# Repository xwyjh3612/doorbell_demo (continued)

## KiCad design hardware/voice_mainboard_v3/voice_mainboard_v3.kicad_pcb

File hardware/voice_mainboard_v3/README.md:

# 语音对讲V3主板工程

本版已完成可编辑的KiCad 9原理图、100×75mm四层PCB及实际装配BOM。独立检查通过：**ERC 0、DRC 0、未连接0，490项引脚/网络映射与原理图、PCB一致**。这是首板工程复核版本，尚未完成电源、封装、装配与整机验收，尚未生产放行。

板上直接焊ML307R-DL，集成充电、备用升压、自动电源切换、欠压控制和电池采样。ESP32-S3、INMP441、MAX98357沿用完整模块，通过线束连接。本版费用已经将这些外挂模块单独计入“主板总成”；当前架构还没有达到80元整机目标。

## 查看设计

- [交互预览](exports/review.html)：实际PCB正反面、接口、供电路径、检查范围与费用。
- [工程入口](voice_mainboard_v3.kicad_pro)、[PCB](voice_mainboard_v3.kicad_pcb)、[原理图](voice_mainboard_v3.kicad_sch)。
- [原理图SVG](exports/schematic/voice_mainboard_v3.svg)：网络标签同名即连接。
- [独立检查结果](exports/validation.json)、[DRC报告](exports/current-drc.json)、[ERC报告](exports/erc.json)。
- [实际局部走线及条件功率核算](exports/power-audit.json)：去耦电容角色、走线长度和明确的估算边界。
- [费用表](../../outputs/voice-v3-20261122/语音对讲V3主板费用.xlsx)、[费用说明](cost/费用说明.md)。
- [网站价格复核与降本候选](cost/网站价格复核与降本候选.md)：重新查询36个料号，区分原型号公开价、便宜候选及未取得的采购阶梯价。
- [ML307阶梯价修正及型号对比](cost/ML307阶梯价修正及型号对比.md)：用户提供完整档位后，确认R-DL的16.50元是1000只价格；5只和100只费用已修正，C-DL尚未批准替换。
- [50元量产主板目标](cost/50元量产主板目标.md)：按1000台、含ESP32/4G/音频及UPS制定控制目标；尚未完成对应集成设计、报价及实机验证，不能作为已实现成本。
- [工程复核包](exports/voice-v3-engineering-review.zip)：KiCad、Gerber/钻孔、BOM、坐标与检查证据；制造文件尚未生产放行。
- [装配BOM](cost/assembly-bom.csv)、[SMT坐标](cost/positions.csv)、[物料和工艺数据](cost/bom-and-process.json)。
- [工程复核及首板验收](工程复核及首板验收.md)：未完成项目与分步上电办法。

176个封装包括4个机械孔、11个测试点；默认装配128个SMT器件、23个插件，另10个器件DNP。49种SMT物料共431个电气焊点；8种插件共97个物理焊点，开关四条腿均计入插件人工。电池端子为插件，裸模组及自建电源芯片封装的SMT属性已补全；原生坐标导出的128项与实际BOM逐项核对。

## 供电与UPS

```text
4.5～5.5V圆口 -> F1 -> Q6 -> VIN_PROTECTED -> TPS2117 VIN1
受保护1S电池 -> TPS61230A约4.992V -> TPS2117 VIN2
TPS2117 -> JP4 2-3 -> POWER_BUS
POWER_BUS -> TPS62933P约3.792V -> J19 1-2 -> ML307 VBAT
POWER_BUS -> TPS63061固定5V -> JP1 1-2 -> SYS_5V
SYS_5V -> JP3 1-2 -> ESP32；另供功放和可选雷达
VIN_PROTECTED -> TP4056 100mA -> 受保护1S电池
```

输入为5.5mm外径/2.5mm中心的圆口，中心正极，标称5V/2A。F1为4A PTC，选该额定值用于温度降额余量，整机适配器基准仍是2A。Q6采用在低栅压有明确导通电阻规格的DMP2035U；ML307裸模组始终使用约3.8V支路。

就近备用升压输入去耦为C41，C40另作输入储能。已测保存PCB的局部走线路径并计算条件功率预算。5V/2A不足以承诺模组2A、系统350mA及100mA充电的同时持续满载；4.5V输入下的模组稳压余量也未通过实测。标称电源和瞬时模组电流是不同定义，不能以2A适配器直接替代负载/瞬态验证。

普通单节4.2V满充锂电池包接J2，包内应有独立保护，放电能力至少5A，10k/B3950 NTC接J4。主板提供正常工作欠压滞回及充电温度检测；电池包保护和NTC随外置电池采购。100mA默认充电减少通话期间额外输入负载，GPIO38预留关闭充电，现有固件尚未驱动该功能。

硬件欠压标称约3.14V关闭升压、3.78V恢复。外电优先控制标称约3.98V切出、4.03V切回。比较器为LM393LV，基准为TLV431B；控制网络已跑行为SPICE和电阻容差角落计算，未代表开关电源或完整UPS通过。

## 默认跳线及接口

每个三针电源选择位只安装一个跳帽：JP4 **2-3**为板载UPS正常模式，JP1 **1-2**为系统5V，J19 **1-2**为板载3.8V，JP3 **1-2**为系统给ESP32供电。JP2短接后为雷达供电，基础款可拔掉。

| 接口 | 针序 | 用途 |
|---|---|---|
| J18 ESP32四针TTL | 1 GND，2 TX43，3 RX44，4 5V | TTL RX接TX43、TTL TX接RX44；串口逻辑3.3V |
| J2 电池 | 1 BAT+，2 GND | 受保护单节4.2V体系电池包 |
| J4 温度 | 1 NTC，2 GND | 电池包10k/B3950 NTC |
| J16 可选雷达 | 1 5V，2 GND，3 GPIO6，4 GPIO8 | 雷达TX接GPIO6，雷达RX接GPIO8 |
| J14 INMP441模块 | 3.3V/GND/BCLK14/WS13/DATA12 | 保留现有已调通的音频引脚 |
| J15 MAX98357模块 | 5V/GND/BCLK15/WS16/DATA7 | 功放板与扬声器输出接法沿用现有模块 |
| J17 外部呼叫按钮 | GPIO0/GND | 常开按钮；SW1同时为BOOT/呼叫 |
| J19 模组电源选择 | 1板载3.8V，2模组VBAT，3外部3.8V | 用于分支隔离和返修 |
| J20 外部模组供电 | 3.8V/GND | 可单独验证模组支路 |
| J22 USB Host预留 | GND/D+GPIO20/D−GPIO19 | 默认DNP，后续选装验证 |

J13是2×15信号线束接口，针序在原理图和design.json中，不能直接套接未知型号开发板。GPIO2预留电池ADC、GPIO9控制采样开关；开启后建议等待60ms再取样，比例2.5，电量只作估算。电池采样、充电抑制、GPIO11/21模组开机/复位驱动尚未集成到当前业务固件；首板先通过J6按模组手册进行手动开机验证。

四针TTL采用手动BOOT/RESET进下载方式。正常用主电供电并只接TTL的GND/TX/RX；JP3用于选择TTL供电给ESP32支路。SW2复位ESP32开发板EN。

## 当前AT与USB预留

默认R26/R27/R30贴装，R28/R29/R31/J22不贴，ML307 USB供电脑维修使用。Host选装时两组选装料互换，避免双主机或VBUS源并接。USB的VBUS只作模组检测，不是VBAT主电源。

官方ESP WebRTC协议和组件、当前业务固件及主动丢旧包策略没有因本次画板而更改。PCB中的USB通路是后续实验接口，当前40轮使用UART AT。

## 板层与制造复核

1.6mm四层：F.Cu/B.Cu各1oz，内层各0.5oz；In1为连续参考地，信号和电源不在该层切割回流。当前设计外层到参考层介质0.18mm，中心介质1.135mm，介电常数4.2是计算输入。实际生产叠层及RF约50Ω、USB约90Ω需与板厂确认后复核。

最小线宽/间距0.2mm；U11同一封装相邻焊盘按厂家DGK形状使用0.15mm例外，走线规则仍保持0.2mm。现有21个过孔采用0.45/0.2mm，其余主要为0.6/0.3mm。试将小孔扩大到0.3mm会发生间距冲突，当前工程保留原孔，并按0.2mm工艺计算板费。

原理图更新使用generate_schematic.py，独立校验使用verify_design.py。build_bom.py读取保存的PCB与已记录公开物料参考，build_cost.py读取实际数量加工计算记录。生成早期摆放的generate_integrated属于搭建过程，运行会替换手工布线；当前工程以保存的kicad_pcb为准。

最后一次装配分类修正后，加工费按原有公开数量费率调整估算，旧响应与调整参数均保留；当前修正参数未获得新的公开响应，不当作厂家最新报价。derive_processing_budget.py保留该预算依据和假设，正式生产费用仍需完整BOM/DFM核价。

工程包不含早期失败的过孔/去耦位置探查PCB。package-manifest.json列出每个交付文件的SHA256；package_review.py按明确清单打包，避免将中间错误报告误认为最终结果。导出的fabrication-unreleased只用于DFM复核。

## 首板与费用边界

电源启动、负载、UPS切换、充电终止、温升及ML307/SIM/圆口实际装配尚待验收。没有完整ESP32/ML307/射频/音频联合仿真，也没有证明新PCB达到90%或99%成功率。

费用表按此版实际板和全部板载物料计算，分别列出5/100/1000片。外挂ESP32/音频、线束和装配预算独立可改。板厂指定叠层、阻抗、起订数量和模组装配工艺尚未取得整单报价，已单列工程预算预留。1000片ML307的5元另列为未确认条件，不作为已谈妥单价。

40轮旧样机连续性测试已经结束：33轮各自满1800秒、7轮中断；1次电脑监督器中断排除并补测。另在挂断阶段捕获ESP异常，不能把媒体通过数量当作完整流程无故障数量。见[最终实机回归记录](../../tests/at_recovery_batch_20261121.md)。这些测试使用现有手工接线设备，不是新PCB验收。

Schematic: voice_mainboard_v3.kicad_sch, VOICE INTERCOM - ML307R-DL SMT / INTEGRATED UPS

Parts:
C1, C4, C5, C6, C7, C32, C33, C34, C35, C36, C40, C41, C42, C43, C44: CL21A226MOCLRNC C398815; C_0805_2012Metric
C2, C3, C11, C13, C14, C15, C16, C17, C18, C20, C27, C28, C30, C31, C50: CL10B104KB8NNNC C1591; C_0603_1608Metric
C8, C9: APXE6R3ARA221MF61G C2161900; CP_Elec_6.3x5.8
C10, C26, C38, C39, C53: CL21A106KAYNNNE C15850; C_0805_2012Metric
C12, C37: CL10C330JB8NNNC; C_0603_1608Metric
C19, C29, C45, C51: CL10B103KB8NNNC; C_0603_1608Metric
C21, C22, C23: CL10C330JB8NNNC [DNP]; C_0603_1608Metric; not fitted
C24, C25: RF MATCH SHUNT DNP [DNP]; C_0603_1608Metric; not fitted
C46, C47: CL10A105KB8NNNC; C_0603_1608Metric
C48: OCV471M1ATR-1010 C250035; CP_Elec_10x10
C49, C52: CL10C102JB8NNNC; C_0603_1608Metric
D1, D2, D3, D4: PESD5V0U1BA,115 C552574; D_SOD-323
D5: BAT54C,215 C37704; SOT-23
F1: ASMD1812-400-16V C55014590; Fuse_1812_4532Metric
J1: HX DC005-2.5-T 3A C18357600; HX_DC005_2p5_T
J2: BATTERY PACK 1S 4.2V >=5A; PIN1+ PIN2GND; DG350_3.5_2P
J4: PACK NTC 10k B3950; PinHeader_1x02_P2.54mm_Vertical
J6: MANUAL PWRKEY HOLD 2-3.5s; PinHeader_1x02_P2.54mm_Vertical
J7: RESET SERVICE ONLY; PinHeader_1x02_P2.54mm_Vertical
J8: DOWNLOAD STRAP - OPEN NORMAL; PinHeader_1x02_P2.54mm_Vertical
J9: MODEM DEBUG 1V8 ONLY; PinHeader_1x04_P2.54mm_Vertical
J10: JAE SF72S006 SIM CANDIDATE; JAE_SIM_Card_SF72S006
J11: LTE ANT U.FL; U.FL_Hirose_U.FL-R-SMT-1_Vertical
J12: USB SERVICE VBUS DM DP GND; PinHeader_1x04_P2.54mm_Vertical
J13: ESP32-S3 SIGNAL HARNESS; USB AT J22; PinHeader_2x15_P2.54mm_Vertical
J14: INMP441 3V3; PinHeader_1x05_P2.54mm_Vertical
J15: MAX98357 5V; PinHeader_1x05_P2.54mm_Vertical
J16: RADAR OPTIONAL TX6 RX8; PinHeader_1x04_P2.54mm_Vertical
J17: CALL BUTTON NORMALLY OPEN; PinHeader_1x02_P2.54mm_Vertical
J18: ESP FLASH TTL GND TX43 RX44 5V; PinHeader_1x04_P2.54mm_Vertical
J19: VBAT SELECT BUCK / MODEM / EXT 3V8; PinHeader_1x03_P2.54mm_Vertical
J20: EXTERNAL 3V8 ONLY NEVER 5V; PinHeader_1x02_P2.54mm_Vertical
J21: BENCH REGULATED 5V ONLY; PinHeader_1x02_P2.54mm_Vertical
J22: USB HOST GND DP20 DM19 [DNP]; PinHeader_1x03_P2.54mm_Vertical; not fitted
JP1: BOARD 5V / SYS / BENCH SELECT ONE; PinHeader_1x03_P2.54mm_Vertical
JP2: RADAR POWER REMOVE TO OMIT; PinHeader_1x02_P2.54mm_Vertical
JP3: ESP POWER SYS / ESP / TTL; PinHeader_1x03_P2.54mm_Vertical
JP4: UPS NORMAL 2-3 / DIRECT DIAGNOSTIC 1-2; PinHeader_1x03_P2.54mm_Vertical
L1: SWPA6045S2R2MT C83455; L_Sunlord_SWPA6045S
L2: SWPA6045S1R5MT C98203; L_Sunlord_SWPA6045S
L3: MWSA0603S-1R0MT C112125; L_Sunlord_MWSA0603S
Q1, Q2, Q4, Q5, Q7: 2N7002K-7 C85047; SOT-23
Q3: BSS84,215 C493579; SOT-23
Q6: DMP2035U-7 C110499; SOT-23
R1, R5, R6, R8, R15, R16, R32, R38, R39: 100k; R_0603_1608Metric
R2: 37.4k 0.1%; R_0603_1608Metric
R3, R43, R44, R51: 10k 0.1%; R_0603_1608Metric
R4, R12, R14, R21, R22, R23, R24, R25, R48, R53: 10k; R_0603_1608Metric
R7: 4.7k AUTO ON LINK [DNP]; R_0603_1608Metric; not fitted
R9, R10, R11: 22R; R_0603_1608Metric
R13: 0R RF SERIES; R_0603_1608Metric
R17: 150k 1%; R_0603_1608Metric
R18, R20: 100k 1%; R_0603_1608Metric
R19: 10k 1%; R_0603_1608Metric
R26: 0R USB SERVICE DP; R_0402_1005Metric
R27: 0R USB SERVICE DM; R_0402_1005Metric
R28: 0R USB HOST DP [DNP]; R_0402_1005Metric; not fitted
R29: 0R USB HOST DM [DNP]; R_0402_1005Metric; not fitted
R30: 0R VBUS FROM SERVICE; R_0603_1608Metric
R31: 0R VBUS DETECT FROM SYSTEM DNP [DNP]; R_0603_1608Metric; not fitted
R33, R34: 10k PG; R_0603_1608Metric
R35: 11k 1%; R_0603_1608Metric
R36: 9.1k 1%; R_0603_1608Metric
R37: 3.3k 1%; R_0603_1608Metric
R40: 316k 0.1%; R_0603_1608Metric
R41: 100k 0.1%; R_0603_1608Metric
R42: 3.3k; R_0603_1608Metric
R45: 499k 0.1%; R_0603_1608Metric
R46: 102k 0.1%; R_0603_1608Metric
R47: 2.4M 1%; R_0603_1608Metric
R49, R54: 1M 1%; R_0603_1608Metric
R50: 54.9k 0.1%; R_0603_1608Metric
R52: 3.9M 1%; R_0603_1608Metric
SW1: BOOT / CALL; SW_PUSH_6mm_H4.3mm
SW2: ESP RESET; SW_PUSH_6mm_H4.3mm
TP1: MODEM VBAT; TestPoint_Pad_D1.0mm
TP2: STATE 1V8; TestPoint_Pad_D1.0mm
TP3: NETLIGHT 1V8; TestPoint_Pad_D1.0mm
TP4: DEBUG_ESP_TX43; TestPoint_Pad_D1.0mm
TP5: DEBUG_ESP_RX44; TestPoint_Pad_D1.0mm
TP6: GND; TestPoint_Pad_D1.0mm
TP7: PROTECTED INPUT; TestPoint_Pad_D1.0mm
TP8: POWER BUS; TestPoint_Pad_D1.0mm
TP9: SYSTEM 5V; TestPoint_Pad_D1.0mm
TP10: SYSTEM POWER GOOD; TestPoint_Pad_D1.0mm
TP11: MODEM POWER GOOD; TestPoint_Pad_D1.0mm
U1: ML307R-DL C48982537; ML307R_DL_109_15.8x17.7mm_DRAFT
U2: TPS62933PDRLR C5219254; SOT-583-8
U3, U4, U5: SN74AXC1T45DBVR C2677376; SOT-23-6
U6: TPS63061DSCR C2876326; TPS63061_DSC0010E_3x3mm
U7: TPD2E2U06DCKR-TP C5350871; SOT-323_SC-70
U8: TP4056 C382139; SOIC-8-1EP_3.9x4.9mm_P1.27mm_EP2.29x3mm
U9: TPS61230ARNSR C376005; TI_RNS0007A
U10: TPS2117DRLR C22399676; TI_DRL0008A
U11: LM393LVDGKR C3659248; VSSOP-8_3x3mm_P0.65mm
U12: TLV431BIDBZR C398375; SOT-23

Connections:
ADC_BAT_IO2: C28.1, J13.17, R17.2, R18.1
ADC_EN_IO9: J13.18, Q4.1 (G), R16.1
BAT_DIV_SW: Q3.3 (D), R17.1
BAT_GATE: Q3.1 (G), Q4.3 (D), R15.2
BAT_SENSE_IN: C39.1, C40.1, C41.1, D5.2 (A2), J2.1, L3.1, Q3.2 (S), R15.1, R45.1, R48.1, U8.5 (BAT), U9.4 (VIN)
BENCH_REG_5V: J21.1, JP1.3
BOARD_REG_5V: C34.1, C35.1, C36.1, JP1.1, U6.8 (FB_FIXED_TO_VOUT), U6.9 (VOUT)
BOOT_BTN_IO0: C27.1, J13.16, J17.1, R14.2, SW1.1
BUCK_3V8: C6.1, C7.1, C37.1, J19.1, L1.2, R2.1
BUCK_BST: C3.1, U2.6 (BST)
BUCK_EN: R1.2, U2.2 (EN)
BUCK_FB: C37.2, R2.2, R3.1, U2.8 (FB)
BUCK_SW: C3.2, L1.1, U2.5 (SW)
CHG_DISABLE_IO38: J13.28, Q7.1 (G), R39.1
CHRG_OD: J13.22, R22.2, U8.7 (CHRG)
DBG_RX_1V8: J9.3, U1.38 (DBG_RXD)
DBG_TX_1V8: J9.2, U1.39 (DBG_TXD)
DEBUG_ESP_RX44: J13.26, J18.3, TP5.1
DEBUG_ESP_TX43: J13.25, J18.2, TP4.1
DONE_OD: J13.23, R23.2, U8.6 (STDBY)
ESP_3V3: C13.1, C15.1, C17.1, J13.3, J14.1, R4.1, R14.1, R21.1, R22.1, R23.1, R24.1, R25.1, R33.1, R34.1, U3.1 (VCCA), U3.5 (DIR), U4.1 (VCCA), U5.1 (VCCA), U5.5 (DIR)
ESP_5V: J13.1, JP3.2
ESP_DTR4: J13.7, R5.1, U5.3 (A)
ESP_EN: C30.1, J13.27, R25.2, SW2.1
ESP_RX18: J13.6, U4.3 (A)
ESP_TX17: J13.5, R4.2, U3.3 (A)
ESP_USB_DM19: J22.3, R29.2
ESP_USB_DP20: J22.2, R28.2
EXT_DETECT_GATE: C29.1, Q5.1 (G), R19.2, R20.1
EXT_MODEM_3V8: J19.3, J20.1
EXT_PRESENT_N_IO10: J13.19, Q5.3 (D), R21.2
GND: C1.2, C2.2, C4.2, C5.2, C6.2, C7.2, C8.2, C9.2, C10.2, C11.2, C12.2, C13.2, C14.2, C15.2, C16.2, C17.2, C18.2, C19.2, C20.2, C21.2, C22.2, C23.2, C24.2, C25.2, C26.2, C27.2, C28.2, C29.2, C30.2, C31.2, C32.2, C33.2, C34.2, C35.2, C36.2, C38.2, C39.2, C40.2, C41.2, C42.2, C43.2, C44.2, C46.2, C47.2, C48.2, C49.2, C50.2, C51.2, C52.2, C53.2, D1.2 (A), D2.2 (A), D3.2 (A), D4.2 (A), J1.2 (SLEEVE_MFR2), J2.2, J4.2, J6.2, J7.2, J8.2, J9.1, J10.C5 (GND), J10.CSW (DETECT_COM), J10.SH (SHIELD), J11.2, J12.4, J13.2, J13.4, J13.30, J14.2, J15.2, J16.2, J17.2, J18.1, J20.2, J21.2, J22.1, Q1.2 (S), Q2.2 (S), Q4.2 (S), Q5.2 (S), Q7.2 (S), R3.2, R5.2, R6.2, R7.2, R8.2, R16.2, R18.2, R20.2, R32.2, R35.2, R39.2, R41.2, R44.2, R46.2, R49.2, R51.2, R54.2, SW1.2, SW2.2, TP6.1, U1.1 (GND), U1.10 (GND), U1.27 (GND), U1.34 (GND), U1.36 (GND), U1.37 (GND), U1.40 (GND), U1.41 (GND), U1.45 (GND), U1.46 (GND), U1.47 (GND), U1.48 (GND), U1.70 (GND), U1.71 (GND), U1.72 (GND), U1.73 (GND), U1.88 (GND), U1.89 (GND), U1.90 (GND), U1.91 (GND), U1.92 (GND), U1.93 (GND), U1.94 (GND), U1.95 (GND), U2.1 (RT_1P2MHz), U2.4 (GND), U3.2 (GND), U4.2 (GND), U4.5 (DIR), U5.2 (GND), U6.4 (PS_SYNC), U6.7 (GND), U6.11 (EP_PGND), U7.3 (GND), U8.3 (GND), U8.9 (EP_GND), U9.6 (GND), U10.1 (GND), U11.4 (GND), U12.3 (A)
I2S_AMP_BCLK15: J13.11, J15.3
I2S_AMP_DATA7: J13.13, J15.5
I2S_AMP_WS16: J13.12, J15.4
I2S_MIC_BCLK14: J13.8, J14.3
I2S_MIC_DATA12: J13.10, J14.5
I2S_MIC_WS13: J13.9, J14.4
MODEM_1V8: C14.1, C16.1, C18.1, J9.4, R12.1, U1.24 (VDD_EXT), U3.6 (VCCB), U4.6 (VCCB), U5.6 (VCCB)
MODEM_3V8: C8.1, C9.1, C10.1, C11.1, C12.1, J19.2, TP1.1, U1.42 (VBAT), U1.43 (VBAT)
MODEM_BOOT_N: J8.1, U1.82 (BOOT_MODE)
MODEM_NETLIGHT: TP3.1, U1.16 (NETLIGHT)
MODEM_PWRKEY_N: J6.1, Q1.3 (D), R7.1, U1.7 (PWR_ON_OFF)
MODEM_REG_PG: R34.2, TP11.1, U2.7 (PG)
MODEM_RESET_N: C19.1, J7.1, Q2.3 (D), U1.15 (RESET_N)
MODEM_STATE_1V8: TP2.1, U1.25 (STATE)
M_DTR_1V8: U1.19 (UART0_DTR), U5.4 (B)
M_RX_1V8: U1.17 (UART0_RXD), U3.4 (B)
M_SIM_CLK: R10.1, U1.13 (USIM_CLK)
M_SIM_DATA: R9.1, U1.11 (USIM_DATA)
M_SIM_RESET: R11.1, U1.12 (USIM_RESET)
M_TX_1V8: U1.18 (UART0_TXD), U4.4 (B)
M_USB_DM: R27.1, R29.1, U1.60 (USB_DM)
M_USB_DP: R26.1, R28.1, U1.59 (USB_DP)
NTC_PACK: J4.1, R37.2
POWER_BUS: C4.1, C5.1, C32.1, C33.1, JP4.2, R1.1, TP8.1, U2.3 (VIN), U6.2 (VIN), U6.3 (EN)
POWER_REG_5V: C48.1, C53.1, JP4.3, U10.2 (VOUT), U10.7 (VOUT_DUPLICATE)
PWRKEY_CTL: J13.20, Q1.1 (G), R6.1
RADAR_5V: C26.1, J16.1, JP2.2
RADAR_RX_FROM_IO8: J13.15, J16.4
RADAR_TX_TO_IO6: J13.14, J16.3
RESET_CTL: J13.21, Q2.1 (G), R8.1
REVERSE_GATE: Q6.1 (G), R32.1
RF_ANT: C24.1, R13.1, U1.35 (ANT_MAIN)
RF_FEED: C25.1, J11.1, R13.2
SERVICE_USB_DM: J12.2, R27.2, U7.1 (IO1)
SERVICE_USB_DP: J12.3, R26.2, U7.2 (IO2)
SERVICE_USB_VBUS: J12.1, R30.1
SIM_CLK: C22.1, D2.1 (K), J10.C3 (CLK), R10.2
SIM_DATA: C21.1, D1.1 (K), J10.C7 (IO), R9.2
SIM_DETECT: J10.DSW (DETECT), R12.2, U1.79 (USIM_DET)
SIM_RESET: C23.1, D3.1 (K), J10.C2 (RST), R11.2
SIM_VCC: C20.1, D4.1 (K), J10.C1 (VCC), U1.14 (USIM_PWR)
SYS_5V: C1.1, C2.1, J15.1, JP1.2, JP2.1, JP3.1, R31.1, TP9.1
SYS_AUX: C31.1, U6.6 (VAUX)
SYS_L1: L2.1, U6.1 (L1)
SYS_L2: L2.2, U6.10 (L2)
SYS_REG_PG: R33.2, TP10.1, U6.5 (PG)
TTL_5V: J18.4, JP3.3
UPS_BACKUP_5V: C42.1, C43.1, C44.1, C47.1, R40.1, U9.7 (VOUT), U10.6 (VIN2)
UPS_BAT_UV_SENSE: C51.1, R45.2, R46.1, R47.2, U11.3 (IN_A_POS)
UPS_BOOST_EN: R47.1, R48.2, R49.1, U9.2 (EN), U11.1 (OUT_A)
UPS_BOOST_FB: R40.2, R41.1, U9.3 (FB)
UPS_CBST: C45.1, U9.1 (CBST)
UPS_CHG_CE: Q7.3 (D), R38.2, U8.8 (CE)
UPS_CHG_PROG: R35.1, U8.2 (PROG)
UPS_CTL_VCC: C50.1, D5.3 (K_COMMON), R42.1, R53.1, U10.5 (MODE), U11.8 (VCC)
UPS_EXT_SENSE: C52.1, R50.2, R51.1, R52.2, U11.5 (IN_B_POS)
UPS_EXT_VALID: R52.1, R53.2, R54.1, U10.4 (PR1), U11.7 (OUT_B)
UPS_PG_OD: J13.24, R24.2, U10.8 (ST)
UPS_REF_0V62: C49.1, R43.2, R44.1, U11.2 (IN_A_NEG), U11.6 (IN_B_NEG)
UPS_REF_1V24: R42.2, R43.1, U12.1 (REF), U12.2 (K)
UPS_SW: C45.2, L3.2, U9.5 (SW)
UPS_TEMP: R36.2, R37.1, U8.1 (TEMP)
USB_DETECT_5V: R30.2, R31.2, U1.61 (USB_VBUS)
VIN_DC: F1.1, J1.4 (CENTER_PLUS_MFR4), R19.1
VIN_FUSED: F1.2, Q6.3 (D)
VIN_PROTECTED: C38.1, C46.1, D5.1 (A1), JP4.1, Q6.2 (S), R36.1, R38.1, R50.1, TP7.1, U8.4 (VCC), U10.3 (VIN1)

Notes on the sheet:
01 UPS RESERVE / GATED BATTERY ADC
02 5V TO 3.8V MODEM BUCK
03 ML307R-DL / 1.8V UART
04 POWERKEY / RESET / DEBUG
05 SIM / RF / USB HOST-SERVICE SELECT
06 ESP / AUDIO / BUTTON / RADAR
07 SEPARATE SYSTEM 5V CONVERTER
08 BATTERY PACK / CHARGER / NTC
09 BACKUP BOOST / AUTOMATIC POWER MUX
10 HARDWARE UV HYSTERESIS / SOURCE THRESHOLD
UPS: U8 TP4056 100mA / U9 TPS61230A 4.992V / U10 TPS2117. Protected >=5A 1S pack at J2, 10k/B3950 NTC at J4.
Battery ADC: GPIO2 ADC1_CH1, enable GPIO9; 150k/100k + 100nF; Vbat = 2.5 x calibrated ADC volts. Protected 1S 4.2V assumed.
No firmware changes: optional radar RX GPIO6 / reserved TX GPIO8; button GPIO0; modem PWRKEY GPIO11 / RESET GPIO21 proposed only.
USB: SERVICE R26/R27/R30 OR HOST R28/R29/R31 + J22, never both. J22 = GND/DP20/DM19. J13 pin28 charge-disable GPIO38, pin29NC. Hardware USB test pending.
J19 VBAT: one shunt only 1-2 internal buck OR 2-3 external regulated 3.8V at J20; none isolates modem. Never 5V at J20.
INPUT: nominal 5V/2A, 4.5-5.5V range. JP4 2-3 = onboard UPS NORMAL; 1-2 = adapter diagnostic bypass. Only one shunt.
JP1 one shunt: 1-2 BOARD_REG_5V / SYS_5V OR 2-3 SYS_5V / BENCH_REG_5V. Both sources regulated 5V.

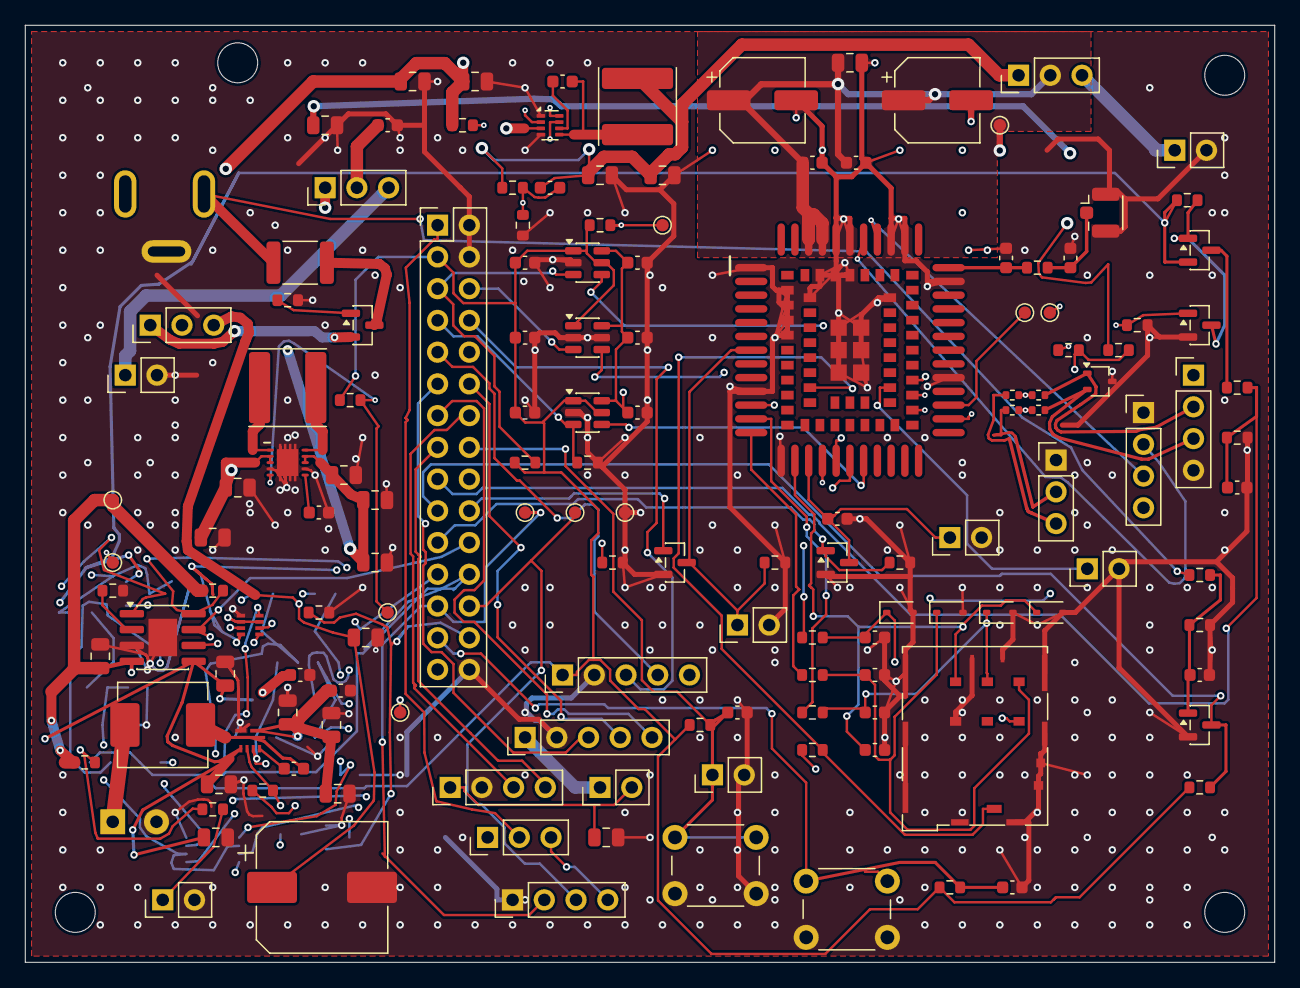
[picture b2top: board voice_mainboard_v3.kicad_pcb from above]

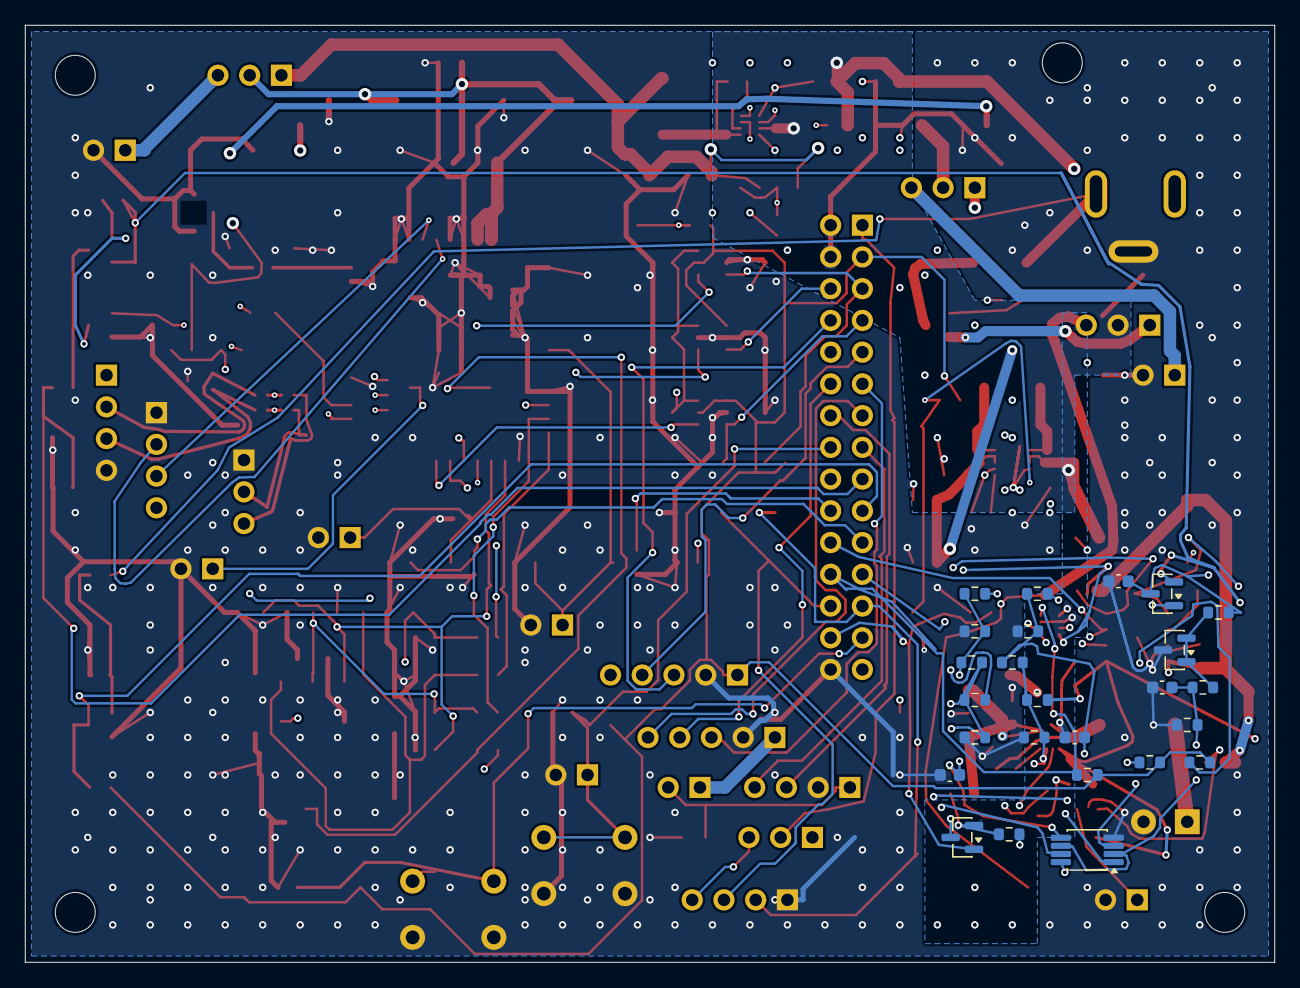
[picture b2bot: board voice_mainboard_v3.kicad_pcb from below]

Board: 4 copper layers, 100.0 x 75.0 mm, 176 parts (25 on the bottom side), 98 nets.

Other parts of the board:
H1, H2, H3, H4: M3 GENERIC; MountingHole_3.2mm_M3

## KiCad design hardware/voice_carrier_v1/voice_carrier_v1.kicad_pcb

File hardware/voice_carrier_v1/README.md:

# 语音对讲V1连接底板草图

阶段更新：当前按[5台模块直供电演示](../../首批5台分阶段实施方案.md)和[量产候选电池＋2～3块专用电源测试PCB](../../集成备用电源打样与电池定型.md)并行推进。成品大UPS退出当前采购推荐。本目录是抽取电源部分和后续集成的设计输入，尚未完成专用电源测试板，不是可直接加工的订单。

当前交付是**可编辑原理图和PCB元件摆放草图**。PCB尚未布线，有132处未完成连接；没有可用于下单的Gerber。90×65mm板框和通用固定孔尚未匹配已购外壳，5V/2A目标也没有整板实测。

首版沿用已调通的ESP32-S3开发板、自研4G板、INMP441、MAX98357和喇叭。模块通过线束接到底板，避免在实物尺寸未知时猜测直插座；芯片级电源集成是新电路，需要独立验证。没有修改ESP32通信协议、固件、主动丢包行为，也没有刷机。

## 文件

- [PCB元件摆放草图](voice_carrier_v1.kicad_pcb)：KiCad 9可编辑，90×65mm、四个通用M3孔。
- [原理图](voice_carrier_v1.kicad_sch)：各器件按真实引脚与网络标签连接，使用随附Voice符号库。
- [带中文说明的首版摆放图](exports/overview.png)、[KiCad摆放预览](exports/placement.svg)、[原理图预览](exports/schematic/voice_carrier_v1.svg)。SVG可放大；原理图按网络标签连接，配合下方供电流程阅读。
- [1:1板框与通用孔位模板](exports/hole-template-1to1.svg)：90×65mm，可按实际大小打印；先量图内20mm标尺确认打印比例。孔位未匹配已购外壳螺柱，不能据此先钻外壳。
- [检查结果](exports/validation.json)：57个电气器件、4个机械孔；原理图ERC和元件摆放几何检查均0违规，132处未布线。检查不证明电源性能。
- [安装物料参考表](pcb-bom.csv)、[机械尺寸核对表](尺寸核对表.md)。BOM中的价格为公开参考/预算，部分通用件尚无固定采购料号。
- [5台与100台预算](../../outputs/pcb-v1-cost/语音对讲5台与100台预算.xlsx)、[费用说明](../../首版5台与100台成本.md)。
- [首批5台贴片/插件与外购模块询价资料](../../outputs/first5-supplier/首批5台采购与商家询价.md)：含数量、待确认料号、可填写报价的Excel和5页电路图PDF。当前用于设计复核和询价，未发布生产文件。

## 供电与接口

```text
稳压外电约5.2V ─┬── TPS2117 VIN1 ─────────┐
                └── TP4056 ─ 受保护1S电池  │
                              │            ├── SYS5V：ESP32、4G、功放
                              └──TPS61230A─┘              └──JP2──可选雷达
                                     VIN2

比较器+基准：外电检测和硬件优先切换
电池欠压监控：独立关闭升压；外电仍可供系统
电池/外电分压：预留ADC接口，具体ESP32 GPIO待分配
```

| 接口 | 本底板引脚次序 | 接法或限制 |
| --- | --- | --- |
| J1 外电 | 1 VIN_EXT，2 GND | 约5.2V稳压输入，绝不超过5.5V；当前适配器料号未固定，输入电压/电流须按负载验证 |
| J2 电池 | 1 VBAT，2 GND | 受保护单节4.2V体系锂电池包；暂按≥5A持续放电选型；不直接接未保护裸电芯 |
| J3 4G电源 | 1 SYS5V，2 GND | 仅接自研板经确认支持5V的板级入口，不能直接给裸ML307的电池入口5V |
| J4 电池NTC | 1 NTC，2 GND | 电池上的10kΩ NTC；B值未冻结；断开NTC按设计暂停充电 |
| J6 4G UART | 1 GND，2 IO17，3 IO18，4 IO4 | ESP TX17→4G RX；ESP RX18←4G TX；IO4→DTR；核对原板逻辑电平 |
| J7 麦克风 | 1 3.3V，2 GND，3 IO14，4 IO13，5 IO12 | BCLK14、WS13、数据12，L/R选择保持当前已验证模块接法 |
| J8 功放 | 1 SYS5V，2 GND，3 IO15，4 IO16，5 IO7 | BCLK15、WS16、数据7；增益/关断脚沿用原模块接法；喇叭接功放两路差分输出 |
| J9 可选雷达 | 1 RADAR5V，2 GND，3 IO6，4 IO8 | 模块TX→第3脚→ESP RX6；模块RX←第4脚←预留ESP TX8；GPIO8当前固件不驱动 |
| JP2 雷达电源 | 1 SYS5V，2 RADAR5V | 基础款不装雷达且不短接；安装模块时可短接；这是人工跳线，未实现软件电源关断 |
| J10 呼叫按钮 | 1 BTN，2 GND | 常开自复位按钮；10k上拉和100n滤波；JP1选择GPIO0或GPIO9 |
| JP1 按钮IO选择 | 1 IO0，2 BTN，3 IO9 | 1–2选择GPIO0，2–3选择GPIO9。旧GPIO0固件使用下拉/基线变化逻辑，新电路需适配，不能宣称插上即呼叫 |
| TP1 / TP2 | IO43 / IO44 | ESP UART0 TX / RX测试焊盘，不带额外供电 |

**J5是自定义2×12线束接口，不能直接套在ESP32开发板排针上。** 从1号方形焊盘起，奇偶脚交错：

| 奇数脚 | 网络 | 偶数脚 | 网络 |
| --- | --- | --- | --- |
| 1 | SYS5V | 2 | GND |
| 3 | ESP输出3.3V | 4 | GND |
| 5 | GPIO17 | 6 | GPIO18 |
| 7 | GPIO4 | 8 | GPIO14 |
| 9 | GPIO13 | 10 | GPIO12 |
| 11 | GPIO15 | 12 | GPIO16 |
| 13 | GPIO7 | 14 | GPIO6 |
| 15 | GPIO8 | 16 | GPIO0 |
| 17 | GPIO9 | 18 | ADC_BAT（GPIO待定） |
| 19 | ADC_EXT（GPIO待定） | 20 | MUX_ST（GPIO待定） |
| 21 | CHRG（GPIO待定） | 22 | DONE（GPIO待定） |
| 23 | GPIO43 | 24 | GPIO44 |

## 电气设计中已算出的值与待验证项

- TPOWER TP4056的2.7kΩ PROG电阻按1100/2700得到约0.407A充电，仍须计入实际芯片偏差与电芯允许充电电流。
- 331k/100k反馈分压给出TPS61230A PWM典型输出5.15045V。基准上下限及电阻误差会改变输出；不能只按典型值保证R60的4.9～5.5V、≤100mV纹波。
- 电池欠压器件是TLV803EA30DBZR，下降阈值标称**3.08V**，不是3.00V；释放延时200ms。欠压后的电池电压回弹可能触发重复启动，要实测并评估关断滞回/锁定策略。
- LM393+TL431B外电检测使用105k/100k分压、5.6M反馈。按2.495V基准、输出低0.2V/高4.9V，外电上升约5.158V、下降约5.070V；这是典型假设，需计入LM393（不是B版）的偏置/失调、TL431误差、供电和温度。适配器的实物最低电压必须高于最坏恢复阈值，尚未确认。
- 9.1k上臂、3.3k串10k NTC下臂在25℃名义分压为0.594VCC；名义45%/80%阈值对应NTC约4.145k/33.1k。仅在B=3950K假设下对应约46℃/0℃，实际窗口须按固定NTC规格和阈值偏差重新核算。
- SYS5V后470µF并不等于切换完全无压降；还要核算总模块电容、ESR、启动浪涌和负载突变。升压局部2×22µF需选择有足够有效容量的实物电容。
- 主板暂未实现受控功放/雷达断电，也没有冻结外电输入保护与USB防倒灌方案。首次验证用有限流的台式电源；开发板USB供电和底板5V不能在隔离未核对时同时连接。
- 电池ADC、外电检测、掉电上报后的省电逻辑尚未加入固件。1000mAh容量是预算输入，不能承诺带着4G持续在线可待机几小时。

## 继续到可打样文件

先取得实物尺寸、固定电池与适配器规格、确认模块输入，再完成电源大电流环路、铜皮/散热、保护及其余布线；检查原厂焊盘、钢网及最终阻容料号。完成ERC/完整DRC、装配与机械复核之后才导出Gerber、钻孔和贴片坐标。

首板需先做电源空载/2A负载/低电池/切换/充满长期插电测量，再接原有通话硬件验证。原固件经过人工测试，不代表新电源PCB已经通过。

## 重建与检查

用KiCad 9 Python运行generate_design.py，普通Python运行generate_schematic.py。使用kicad-cli导出原理图kicadxml网表并运行ERC和PCB DRC后，用KiCad Python运行verify_design.py。检查脚本对比网表、PCB焊盘和设计表的171个已命名引脚连接，明确保留未布线状态；具体计数以validation.json为准。

原厂资料与选型依据见[首版PCB与备用电源选型](../../首版PCB与备用电源选型.md)。

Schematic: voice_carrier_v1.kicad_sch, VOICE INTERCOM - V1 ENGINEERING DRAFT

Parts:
C1, C2, C16: 10u 10V; C_0805_2012Metric
C3, C4, C5: 22u 10V; C_0805_2012Metric
C6: 10n; C_0603_1608Metric
C7, C8: 1u; C_0603_1608Metric
C9: 470u 10V LOW ESR; CP_Radial_D8.0mm_P3.50mm
C10, C11, C12, C13, C14, C15: 100n; C_0603_1608Metric
D1: BAT54C,215; SOT-23
J1: 5.2V INPUT; TerminalBlock_Phoenix_MKDS-1,5-2-5.08_1x02_P5.08mm_Horizont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
J2: 1S BATTERY; TerminalBlock_Phoenix_MKDS-1,5-2-5.08_1x02_P5.08mm_Horizont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
J3: 4G POWER; TerminalBlock_Phoenix_MKDS-1,5-2-5.08_1x02_P5.08mm_Horizont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
J4: BAT NTC; PinHeader_1x02_P2.54mm_Vertical
J5: ESP32 HARNESS; PinHeader_2x12_P2.54mm_Vertical
J6: 4G UART; PinHeader_1x04_P2.54mm_Vertical
J7: INMP441; PinHeader_1x05_P2.54mm_Vertical
J8: MAX98357; PinHeader_1x05_P2.54mm_Vertical
J9: RADAR OPTIONAL; PinHeader_1x04_P2.54mm_Vertical
J10: CALL BUTTON; PinHeader_1x02_P2.54mm_Vertical
JP1: BUTTON IO0 / IO9; PinHeader_1x03_P2.54mm_Vertical
JP2: RADAR POWER; PinHeader_1x02_P2.54mm_Vertical
L1: SWPA6045S1R0NT; L_Sunlord_SWPA6045S
R1: 2.7k; R_0603_1608Metric
R2: 9.1k; R_0603_1608Metric
R3: 3.3k; R_0603_1608Metric
R4: 331k 0.1%; R_0603_1608Metric
R5, R9: 100k 0.1%; R_0603_1608Metric
R6: 100k; R_0603_1608Metric
R7: 1.8k; R_0603_1608Metric
R8: 105k 0.1%; R_0603_1608Metric
R10: 5.6M 1%; R_0603_1608Metric
R11, R16, R17, R18, R19: 10k; R_0603_1608Metric
R12, R13, R15: 100k 1%; R_0603_1608Metric
R14: 150k 1%; R_0603_1608Metric
TP1: IO43; TestPoint_Pad_D1.5mm
TP2: IO44; TestPoint_Pad_D1.5mm
U1: TP4056 TPOWER; SOIC-8-1EP_3.9x4.9mm_P1.27mm_EP2.29x3mm
U2: TPS61230ARNSR; TI_RNS0007A
U3: TPS2117DRLR; TI_DRL0008A
U4: TLV803EA30DBZR; SOT-23
U5: LM393DR; SOIC-8_3.9x4.9mm_P1.27mm
U6: TL431BIDBZR; SOT-23

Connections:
ADC_BAT: C13.1, J5.18, R12.2, R13.1
ADC_EXT: C14.1, J5.19, R14.2, R15.1
BOOST5V: C4.1, C5.1, C8.1, D1.2 (A2), R4.1, U2.7 (VOUT), U3.6 (VIN2)
BOOST_EN: R6.2, U2.2 (EN), U4.2 (RESET_N)
BOOST_FB: R4.2, R5.1, U2.3 (FB)
BTN: C15.1, J10.1, JP1.2, R19.2
CBST: C6.1, U2.1 (CBST)
CHG_PROG: R1.1, U1.2 (PROG)
CHRG: J5.21, R17.2, U1.7 (CHRG)
DONE: J5.22, R18.2, U1.6 (STDBY)
EXT_SENSE: R8.2, R9.1, R10.2, U5.3 (IN1_P)
GND: C1.2, C2.2, C3.2, C4.2, C5.2, C7.2, C8.2, C9.2, C10.2, C11.2, C12.2, C13.2, C14.2, C15.2, C16.2, J1.2, J2.2, J3.2, J4.2, J5.2, J5.4, J6.1, J7.2, J8.2, J9.2, J10.2, R1.2, R5.2, R9.2, R13.2, R15.2, U1.3 (GND), U1.9 (EP), U2.6 (GND), U3.1 (GND), U4.1 (GND), U5.4 (GND), U5.5 (IN2_P), U6.3 (A)
IO0: J5.16, JP1.1
IO4: J5.7, J6.4
IO6: J5.14, J9.3
IO7: J5.13, J8.5
IO8: J5.15, J9.4
IO9: J5.17, JP1.3
IO12: J5.10, J7.5
IO13: J5.9, J7.4
IO14: J5.8, J7.3
IO15: J5.11, J8.3
IO16: J5.12, J8.4
IO17: J5.5, J6.2
IO18: J5.6, J6.3
IO43: J5.23, TP1.1
IO44: J5.24, TP2.1
MUX_ST: J5.20, R16.2, U3.8 (ST)
NTC: J4.1, R3.2
PRIORITY: R10.1, R11.2, U3.4 (PR1), U5.1 (OUT1)
RADAR5V: C16.1, J9.1, JP2.2
REF2V5: R7.2, U5.2 (IN1_N), U5.6 (IN2_N), U6.1 (K), U6.2 (REF)
SW: C6.2, L1.2, U2.5 (SW)
SYS5V: C9.1, J3.1, J5.1, J8.1, JP2.1, U3.2 (VOUT), U3.7 (VOUT)
TEMP: R2.2, R3.1, U1.1 (TEMP)
V3V3: J5.3, J7.1, R16.1, R17.1, R18.1, R19.1
VBAT: C2.1, C3.1, C10.1, J2.1, L1.1, R6.1, R12.1, U1.5 (BAT_CHARGE), U2.4 (VIN), U4.3 (VDD)
VCTL: C11.1, D1.3 (K_COMMON), R7.1, R11.1, U3.5 (MODE), U5.8 (VCC)
VIN_EXT: C1.1, C7.1, C12.1, D1.1 (A1), J1.1, R2.1, R8.1, R14.1, U1.4 (VCC), U1.8 (CE), U3.3 (VIN1)

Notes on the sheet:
01 INPUT / CHARGE / BATTERY TEMPERATURE
02 BATTERY BOOST / HARDWARE UNDERVOLTAGE
03 AUTOMATIC SOURCE SELECTION
04 MEASUREMENT / BUTTON / RADAR POWER
05 EXISTING MODULE HARNESS INTERFACES
POWER FLAGS: external/battery/ESP32 3V3 supplies and diode-OR VCTL. Protected 1S pack required.
Radar is optional: J9 pin 3 = module TX -> ESP32 GPIO6. Pin 4 = module RX <- reserved GPIO8.
Button and battery monitoring need firmware adaptation; ADC GPIO assignment and module mechanical fit remain open.

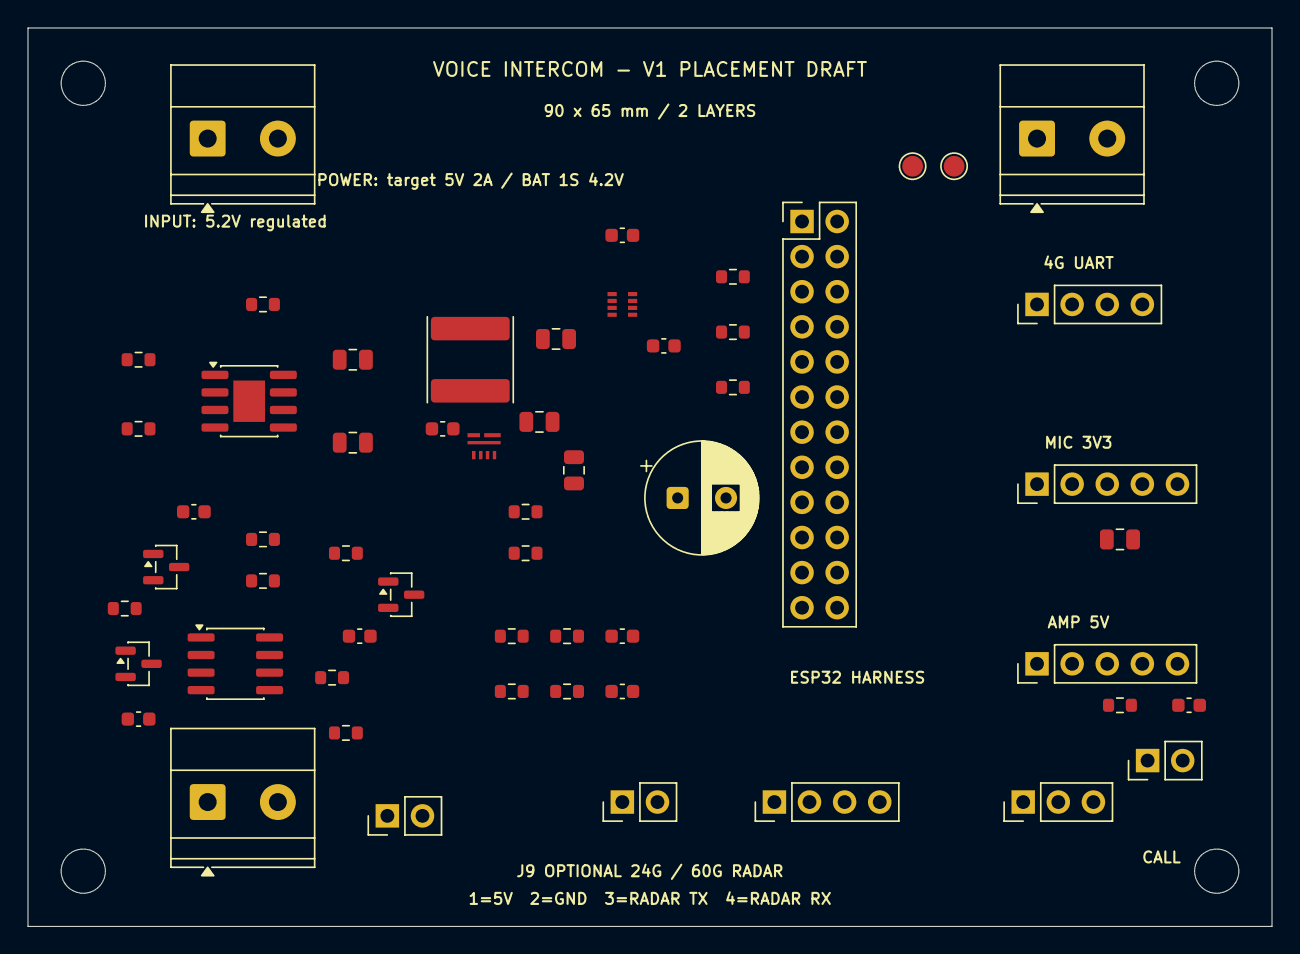
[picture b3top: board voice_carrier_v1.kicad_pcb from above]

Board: 2 copper layers, 90.0 x 65.0 mm, 61 parts (0 on the bottom side), 39 nets, no tracks yet.

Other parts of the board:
H1, H2, H3, H4: M3; MountingHole_3.2mm_M3

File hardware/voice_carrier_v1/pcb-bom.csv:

Reference,Value,Footprint,Qty,Reference CNY,Source,Status
J1,5.2V INPUT,"TerminalBlock_Phoenix:TerminalBlock_Phoenix_MKDS-1,5-2-5.08_1x02_P5.08mm_Horizontal",1,1.2,,reference/estimate; prototype
J2,1S BATTERY,"TerminalBlock_Phoenix:TerminalBlock_Phoenix_MKDS-1,5-2-5.08_1x02_P5.08mm_Horizontal",1,1.2,,reference/estimate; prototype
J3,4G POWER,"TerminalBlock_Phoenix:TerminalBlock_Phoenix_MKDS-1,5-2-5.08_1x02_P5.08mm_Horizontal",1,1.2,,reference/estimate; prototype
J4,BAT NTC,Connector_PinHeader_2.54mm:PinHeader_1x02_P2.54mm_Vertical,1,0.2,,reference/estimate; prototype
J5,ESP32 HARNESS,Connector_PinHeader_2.54mm:PinHeader_2x12_P2.54mm_Vertical,1,0.8,,reference/estimate; prototype
J6,4G UART,Connector_PinHeader_2.54mm:PinHeader_1x04_P2.54mm_Vertical,1,0.25,,reference/estimate; prototype
J7,INMP441,Connector_PinHeader_2.54mm:PinHeader_1x05_P2.54mm_Vertical,1,0.275,,reference/estimate; prototype
J8,MAX98357,Connector_PinHeader_2.54mm:PinHeader_1x05_P2.54mm_Vertical,1,0.275,,reference/estimate; prototype
J9,RADAR OPTIONAL,Connector_PinHeader_2.54mm:PinHeader_1x04_P2.54mm_Vertical,1,0.25,,reference/estimate; prototype
J10,CALL BUTTON,Connector_PinHeader_2.54mm:PinHeader_1x02_P2.54mm_Vertical,1,0.2,,reference/estimate; prototype
JP1,BUTTON IO0 / IO9,Connector_PinHeader_2.54mm:PinHeader_1x03_P2.54mm_Vertical,1,0.225,,reference/estimate; prototype
JP2,RADAR POWER,Connector_PinHeader_2.54mm:PinHeader_1x02_P2.54mm_Vertical,1,0.2,,reference/estimate; prototype
R1,2.7k,Resistor_SMD:R_0603_1608Metric,1,0.02,,reference/estimate; prototype
R2,9.1k,Resistor_SMD:R_0603_1608Metric,1,0.02,,reference/estimate; prototype
R3,3.3k,Resistor_SMD:R_0603_1608Metric,1,0.02,,reference/estimate; prototype
U1,TP4056 TPOWER,Package_SO:SOIC-8-1EP_3.9x4.9mm_P1.27mm_EP2.29x3mm,1,0.4012,https://item.szlcsc.com/354934.html,reference/estimate; prototype
C1,10u 10V,Capacitor_SMD:C_0805_2012Metric,1,0.15,,reference/estimate; prototype
C2,10u 10V,Capacitor_SMD:C_0805_2012Metric,1,0.15,,reference/estimate; prototype
U2,TPS61230ARNSR,Voice:TI_RNS0007A,1,3.14,https://item.szlcsc.com/348561.html,reference/estimate; prototype
L1,SWPA6045S1R0NT,Inductor_SMD:L_Sunlord_SWPA6045S,1,0.335,https://item.szlcsc.com/98160.html,reference/estimate; prototype
C3,22u 10V,Capacitor_SMD:C_0805_2012Metric,1,0.2,,reference/estimate; prototype
C4,22u 10V,Capacitor_SMD:C_0805_2012Metric,1,0.2,,reference/estimate; prototype
C5,22u 10V,Capacitor_SMD:C_0805_2012Metric,1,0.2,,reference/estimate; prototype
C6,10n,Capacitor_SMD:C_0603_1608Metric,1,0.04,,reference/estimate; prototype
R4,331k 0.1%,Resistor_SMD:R_0603_1608Metric,1,0.08,,reference/estimate; prototype
R5,100k 0.1%,Resistor_SMD:R_0603_1608Metric,1,0.08,,reference/estimate; prototype
U3,TPS2117DRLR,Voice:TI_DRL0008A,1,1.82,https://item.szlcsc.com/24017237.html,reference/estimate; prototype
C7,1u,Capacitor_SMD:C_0603_1608Metric,1,0.06,,reference/estimate; prototype
C8,1u,Capacitor_SMD:C_0603_1608Metric,1,0.06,,reference/estimate; prototype
C9,470u 10V LOW ESR,Capacitor_THT:CP_Radial_D8.0mm_P3.50mm,1,1,,reference/estimate; prototype
U4,TLV803EA30DBZR,Package_TO_SOT_SMD:SOT-23,1,1.57,https://item.szlcsc.com/5914664.html,reference/estimate; prototype
R6,100k,Resistor_SMD:R_0603_1608Metric,1,0.02,,reference/estimate; prototype
C10,100n,Capacitor_SMD:C_0603_1608Metric,1,0.06,,reference/estimate; prototype
D1,"BAT54C,215",Package_TO_SOT_SMD:SOT-23,1,0.044,https://item.szlcsc.com/38684.html,reference/estimate; prototype
U5,LM393DR,Package_SO:SOIC-8_3.9x4.9mm_P1.27mm,1,0.1941,https://item.szlcsc.com/68565.html,reference/estimate; prototype
U6,TL431BIDBZR,Package_TO_SOT_SMD:SOT-23,1,0.2337,https://item.szlcsc.com/42267.html,reference/estimate; prototype
R7,1.8k,Resistor_SMD:R_0603_1608Metric,1,0.02,,reference/estimate; prototype
R8,105k 0.1%,Resistor_SMD:R_0603_1608Metric,1,0.08,,reference/estimate; prototype
R9,100k 0.1%,Resistor_SMD:R_0603_1608Metric,1,0.08,,reference/estimate; prototype
R10,5.6M 1%,Resistor_SMD:R_0603_1608Metric,1,0.02,,reference/estimate; prototype
R11,10k,Resistor_SMD:R_0603_1608Metric,1,0.02,,reference/estimate; prototype
C11,100n,Capacitor_SMD:C_0603_1608Metric,1,0.06,,reference/estimate; prototype
C12,100n,Capacitor_SMD:C_0603_1608Metric,1,0.06,,reference/estimate; prototype
R12,100k 1%,Resistor_SMD:R_0603_1608Metric,1,0.02,,reference/estimate; prototype
R13,100k 1%,Resistor_SMD:R_0603_1608Metric,1,0.02,,reference/estimate; prototype
C13,100n,Capacitor_SMD:C_0603_1608Metric,1,0.06,,reference/estimate; prototype
R14,150k 1%,Resistor_SMD:R_0603_1608Metric,1,0.02,,reference/estimate; prototype
R15,100k 1%,Resistor_SMD:R_0603_1608Metric,1,0.02,,reference/estimate; prototype
C14,100n,Capacitor_SMD:C_0603_1608Metric,1,0.06,,reference/estimate; prototype
R16,10k,Resistor_SMD:R_0603_1608Metric,1,0.02,,reference/estimate; prototype
R17,10k,Resistor_SMD:R_0603_1608Metric,1,0.02,,reference/estimate; prototype
R18,10k,Resistor_SMD:R_0603_1608Metric,1,0.02,,reference/estimate; prototype
R19,10k,Resistor_SMD:R_0603_1608Metric,1,0.02,,reference/estimate; prototype
C15,100n,Capacitor_SMD:C_0603_1608Metric,1,0.06,,reference/estimate; prototype
C16,10u 10V,Capacitor_SMD:C_0805_2012Metric,1,0.15,,reference/estimate; prototype
TP1,IO43,TestPoint:TestPoint_Pad_D1.5mm,1,0,,reference/estimate; prototype
TP2,IO44,TestPoint:TestPoint_Pad_D1.5mm,1,0,,reference/estimate; prototype
H1,M3,MountingHole:MountingHole_3.2mm_M3,1,0,,reference/estimate; prototype
H2,M3,MountingHole:MountingHole_3.2mm_M3,1,0,,reference/estimate; prototype
H3,M3,MountingHole:MountingHole_3.2mm_M3,1,0,,reference/estimate; prototype
H4,M3,MountingHole:MountingHole_3.2mm_M3,1,0,,reference/estimate; prototype

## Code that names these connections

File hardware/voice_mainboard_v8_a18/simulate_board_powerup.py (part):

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def maximum(v,sig,a,z):
    return max(y for t,y in zip(v['time'],v[sig])if a<=t<=z)

assert pins('U18')=={'1':'GND','2':'SYS_5V','3':'VIN_PROTECTED','4':'UPS_PR1',
                     '5':'VIN_PROTECTED','6':'BAT_BOOST_5V','7':'SYS_5V','8':'SUPPLY_BAT_N47'}
assert pins('U16')['8']=='CHG_CE' and pins('U16')['4']=='VIN_PROTECTED'
assert pins('Q7')=={'1':'CHG_DISABLE_IO38','2':'GND','3':'CHG_CE'}
assert pins('J23')=={'1':'BAT_SENSE_IN','2':'CELL_NEG','3':'CELL_NTC'}
assert fps['C5'].IsDNP(), 'Do not count the unpopulated C5 as hold-up capacitance'

path_data={
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    sample(label,v,signals)
    ratio=at(v,'v(BAT_TEMP)',.002)/5
    metrics={'battery_source_V':cell_V,'TEMP_to_VCC_ratio':ratio,
       'CE_GPIO38_low_V':at(v,'v(CHG_CE)',.002),'CE_GPIO38_high_V':at(v,'v(CHG_CE)',.004),
       'ADC_disabled_V':at(v,'v(BAT_ADC2)',.002),
       'ADC_enabled_at_12ms_V':at(v,'v(BAT_ADC2)',.012),
       'ADC_enabled_at_40ms_V':at(v,'v(BAT_ADC2)',.040),
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
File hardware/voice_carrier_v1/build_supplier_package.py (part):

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begin('电量/外电检测、状态与按钮',4)
section('ADC分压与滤波',45,130,1510,330)
group_passives(['R12','R13','C13','R14','R15','C14'],80,245,3,470,125)
note(['ADC_BAT = VBAT / 2；ADC_EXT = VIN_EXT x 0.4。ADC GPIO未分配，固件待适配。'],80,433)
section('3.3V上拉状态输出',45,480,695,390)
group_passives(['R16','R17','R18'],85,585,1,0,110)
note(['MUX_ST、CHRG、DONE仅用3.3V上拉。'],80,900)
section('常开自复位呼叫按钮',760,480,795,455)
connector('J10',785,542,320);connector('JP1',1145,542,380)
passive('R19',795,785);passive('C15',1170,785)
note(['按钮两端接BTN/GND。JP1：1-2选GPIO0，2-3选GPIO9。',
      '推荐避开GPIO0启动绑带；GPIO9和明确按下/消抖需固件适配。',
      '当前固件不是直接匹配新按钮电路，不由贴片商家自行更改。'],785,866)
end(4)
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
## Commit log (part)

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2026-03-28 gpt增加通话状态管理
